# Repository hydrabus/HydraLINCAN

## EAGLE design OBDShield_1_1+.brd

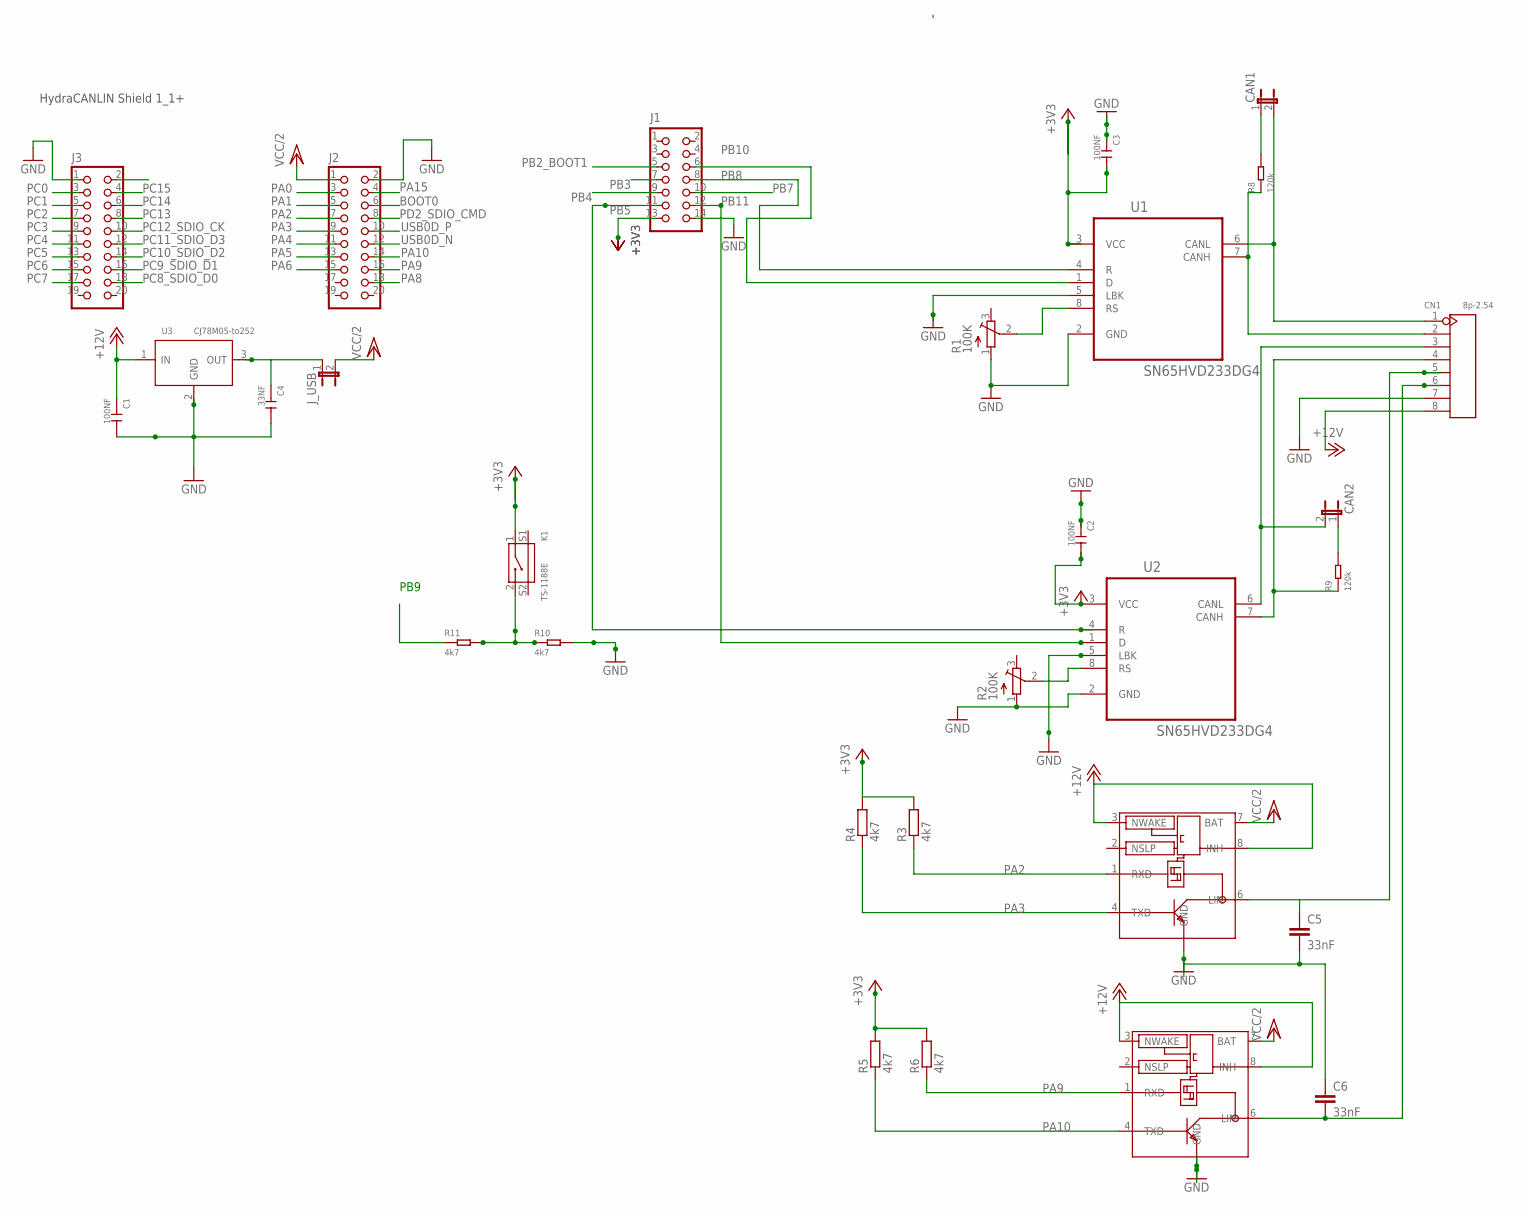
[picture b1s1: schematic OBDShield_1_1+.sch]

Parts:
C1, C2, C3: 100NF; C0805
C4: 33NF; C0805
C5, C6: 33nF; 1206
CAN1, CAN2: JP1E; JP1
CN1: 8p-2.54; H8-2.54
J1: HYDRABUS_SHIELD_CON_HEADER_2X07; HYDRABUS_SHIELD_M2X7
J2, J3: HYDRABUS_SHIELD_CON_HEADER_2X10; HYDRABUS_SHIELD_M2X10
J_USB: JP1E; JP1
K1: TS-1188E; SW4-SMD-7.0X3.5X3.5MM-90D
LIN1, LIN2: TJA1020SO8; SO8
R1, R2: 100K; SM-42/43A
R3, R4, R5, R6: 4k7; M1206
R8, R9: 120k; R1206
R10, R11: 4k7; R1206
U1, U2: SN65HVD233DG4; SOIC127P600X175-8N
U3: CJ78M05-to252; TO-252

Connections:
+3V3: C2.2, C3.2, J1.13, K1.1, R3.2, R4.2, R5.2, R6.2, U1.3 (VCC), U2.3 (VCC)
+12V: C1.1, CN1.8, LIN1.3 (NWAKE), LIN1.8 (INH), LIN2.3 (NWAKE), LIN2.8 (INH), U3.1 (IN)
BOOT0: J2.6
GND: C1.2, C2.1, C3.1, C4.2, C5.2, C6.1, CN1.7, J1.14, J2.2, J3.1, LIN1.5 (GND), LIN2.5 (GND), R1.1 (A), R2.1 (A), R10.2, U1.2 (GND), U1.5 (LBK), U2.2 (GND), U2.5 (LBK), U3.2 (GND)
unnamed: R1.2 (S), U1.8 (RS)
unnamed: C5.1, CN1.5, LIN2.6 (LIN)
unnamed: C6.2, CN1.6, LIN1.6 (LIN)
unnamed: CAN1.2, CN1.1, U1.6 (CANL)
unnamed: CN1.2, R8.1, U1.7 (CANH)
unnamed: CAN2.2, CN1.3, U2.6 (CANL)
unnamed: CN1.4, R9.1, U2.7 (CANH)
unnamed: C4.1, J_USB.1, U3.3 (OUT)
unnamed: CAN2.1, R9.2
unnamed: R2.2 (S), U2.8 (RS)
unnamed: CAN1.1, R8.2
unnamed: K1.2, R10.1, R11.2
PA0: J2.3
PA1: J2.5
PA2: J2.7, LIN2.1 (RXD), R3.1
PA3: J2.9, LIN2.4 (TXD), R4.1
PA4: J2.11
PA5: J2.13
PA6: J2.15
PA8: J2.18
PA9: J2.16, LIN1.1 (RXD), R6.1
PA10: J2.14, LIN1.4 (TXD), R5.1
PA15: J2.4
PB2_BOOT1: J1.5
PB3: J1.7
PB4: J1.9
PB5: J1.11, U2.4 (R)
PB7: J1.10, R11.1
PB8: J1.8, U1.4 (R)
PB10: J1.6, U1.1 (D)
PB11: J1.12, U2.1 (D)
PC0: J3.3
PC1: J3.5
PC2: J3.7
PC3: J3.9
PC4: J3.11
PC5: J3.13
PC6: J3.15
PC7: J3.17
PC8_SDIO_D0: J3.18
PC9_SDIO_D1: J3.16
PC10_SDIO_D2: J3.14
PC11_SDIO_D3: J3.12
PC12_SDIO_CK: J3.10
PC13: J3.8
PC14: J3.6
PC15: J3.4
PD2_SDIO_CMD: J2.8
USB0D_N: J2.12
USB0D_P: J2.10
VCC/2: J2.1, J_USB.2, LIN1.7 (BAT), LIN2.7 (BAT)

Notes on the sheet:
PB9
HydraCANLIN Shield 1_1+

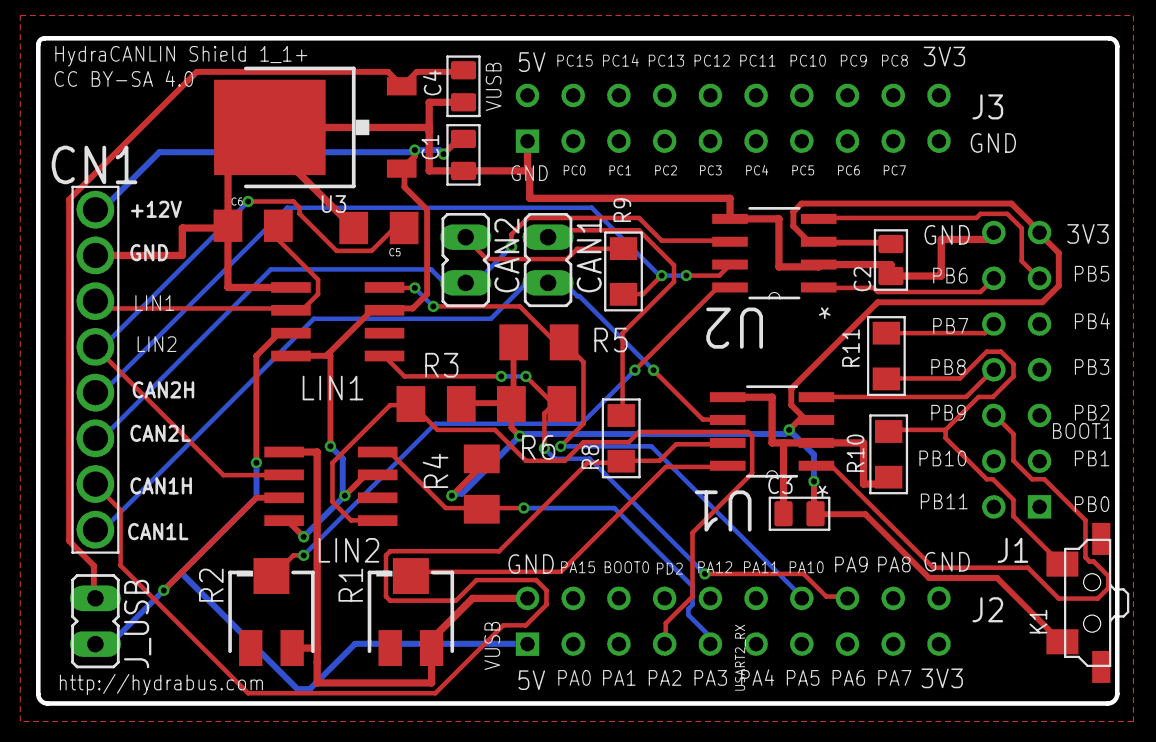
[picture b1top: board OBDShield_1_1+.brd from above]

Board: 2 copper layers, 59.9 x 37.0 mm, 29 parts (0 on the bottom side), 25 nets.

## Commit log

2017-09-17 OBDShield 1.1+ Based on OBDShield.brd / .sch see OBDShield_1_1+_Readme.md for more details

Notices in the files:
OBDShield_1_1+.brd:
CC BY-SA 4.0
